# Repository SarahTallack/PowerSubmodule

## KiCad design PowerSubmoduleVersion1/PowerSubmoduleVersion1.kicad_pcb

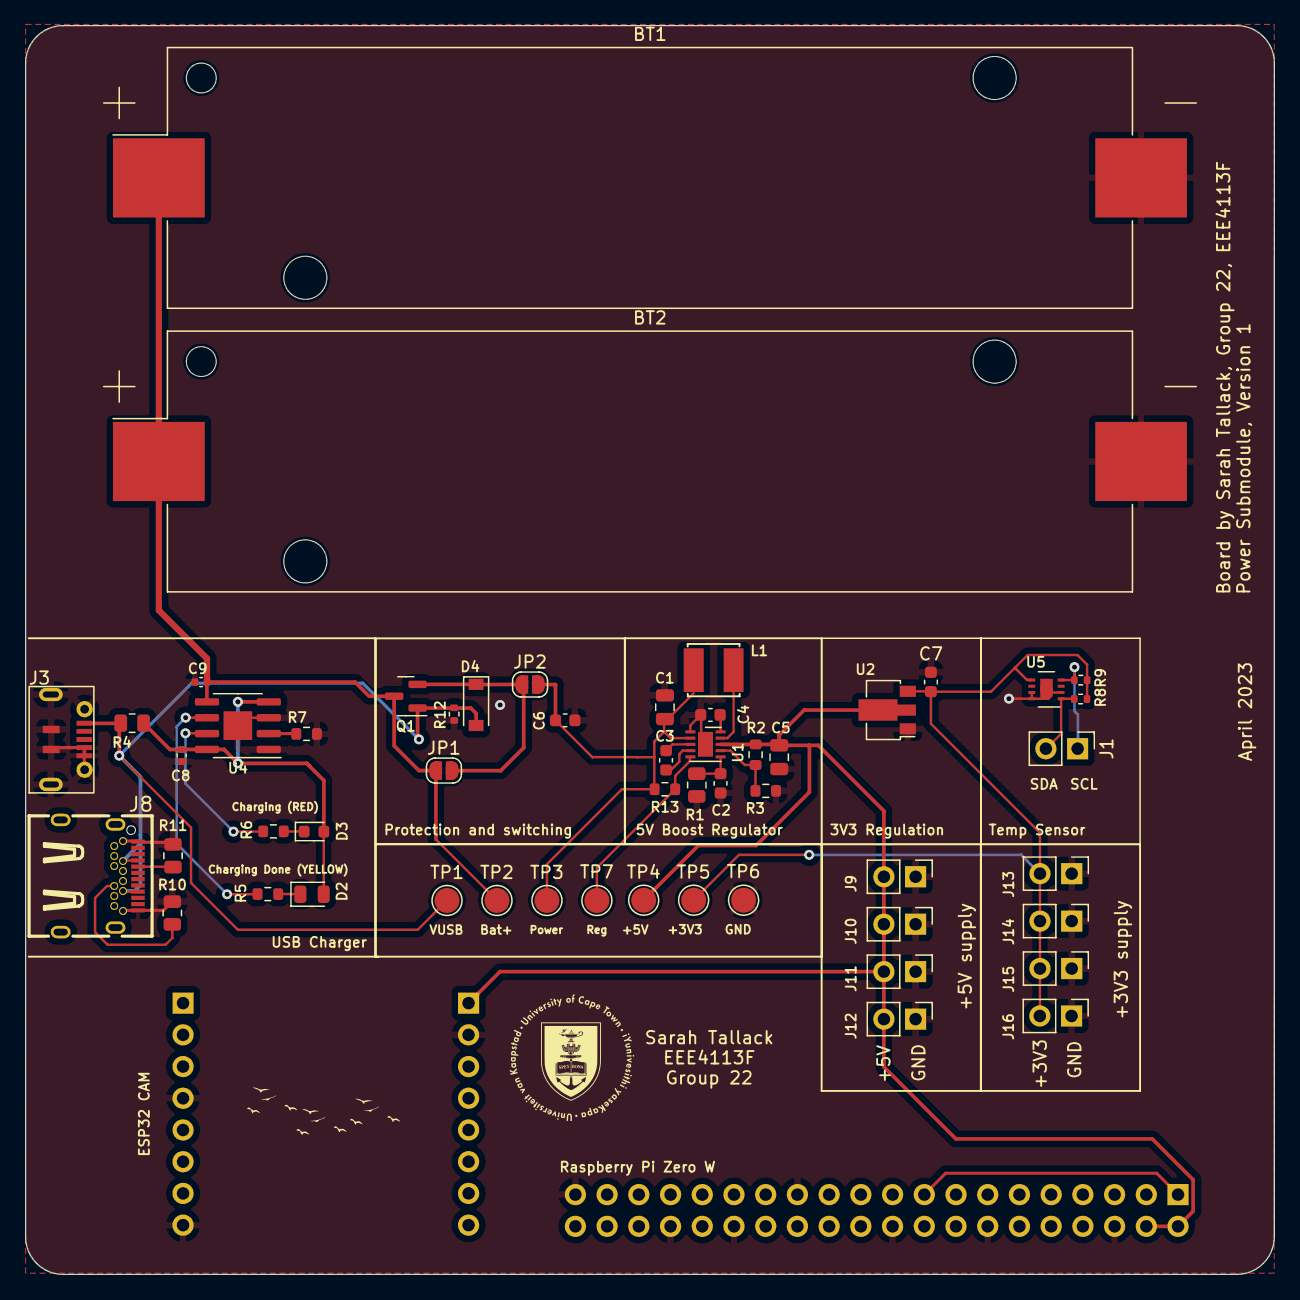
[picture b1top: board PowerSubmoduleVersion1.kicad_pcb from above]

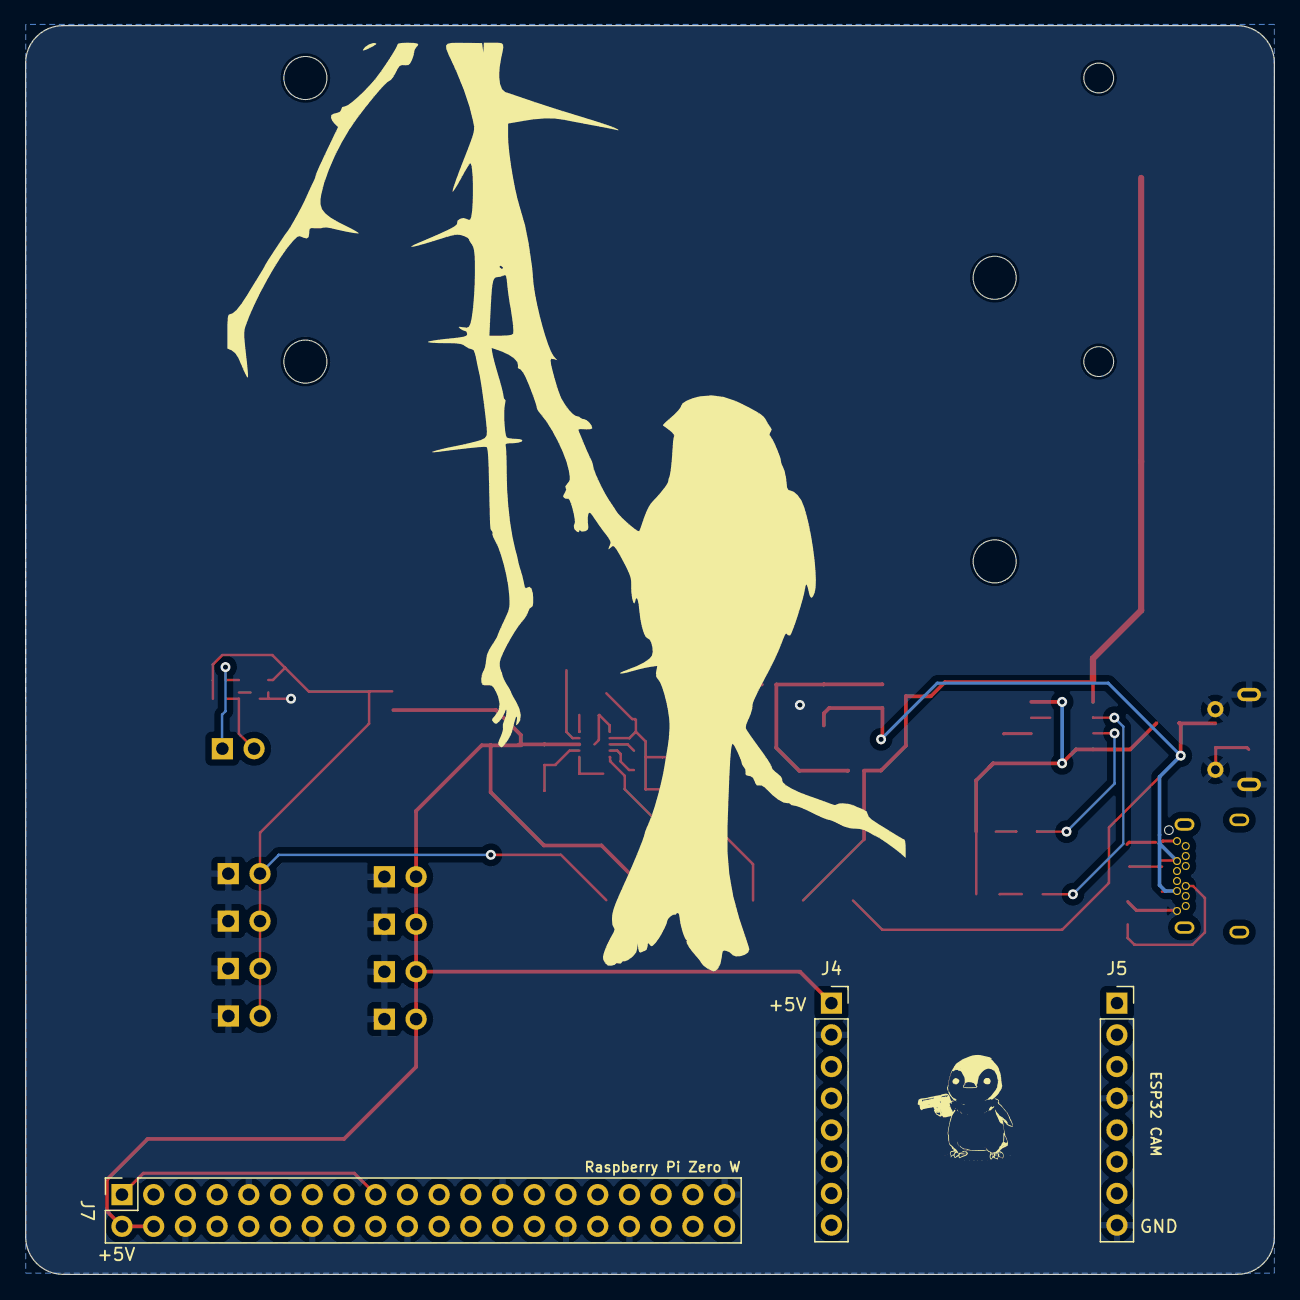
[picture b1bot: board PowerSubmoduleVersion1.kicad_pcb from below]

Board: 2 copper layers, 100.0 x 100.0 mm, 56 parts (3 on the bottom side), 25 nets.

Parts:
BT1, BT2: Li-Ion Battery; BatteryHolder_Keystone_1042_1x18650
C1: 4.7u; C_0805_2012Metric
C2, C3, C4, C6, C7: 100n; C_0603_1608Metric
C5: 1u; C_0805_2012Metric
C8, C9: 10uF; C_0402_1005Metric
D2: YLED; LED_0805_2012Metric
D3: RLED; LED_0603_1608Metric
D4: Diode; D_SOD-123
J1, J9, J10, J11, J12, J13, J14, J15, J16: Conn_01x02_Male; PinHeader_1x02_P2.54mm_Vertical
J3: USB_Micro_B_Female_Connector; C404969_Micro_USB
J4, J5: Conn_01x08_Male; PinSocket_1x08_P2.54mm_Vertical
J7: GPIO; PinSocket_2x20_P2.54mm_Vertical
J8: USB_C_Receptacle; USB-TYPE-C-TH_USB-306A-B-SU
JP1, JP2: Jumper_2_Open; SolderJumper-2_P1.3mm_Open_RoundedPad1.0x1.5mm
L1: 4.7u; IND-SMD_L4.0-W4.0
Q1: Si2301CDS; SOT-23
R1: 200k; R_0805_2012Metric
R2: 180k; R_0603_1608Metric
R3: 20k; R_0603_1608Metric
R4: 330m; R_0805_2012Metric
R5, R6, R13: 1k; R_0603_1608Metric
R7: 1.2k; R_0603_1608Metric
R8, R9: 10k; R_0402_1005Metric
R10, R11: 5.1k; R_0805_2012Metric
R12: 100k; R_0402_1005Metric
TP1, TP2, TP3, TP4, TP5, TP6, TP7: TestPoint; TestPoint_Pad_D2.0mm
U1: TPS63030DSKR; WSON-10-1EP_2.5x2.5mm_P0.5mm_EP1.2x2mm
U2: HT75xx-1-SOT89; SOT-89-3
U4: TP4056_1; HSOP-8-1EP_3.9x4.9mm_P1.27mm_EP2.3x2.3mm
U5: SHT30-DIS; Sensirion_DFN-8-1EP_2.5x2.5mm_P0.5mm_EP1.1x1.7mm

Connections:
/Microcontrollers/+3V3: J7.1, J7.17
/Microcontrollers/+5VReg: C5.2, J4.1, J7.2, J7.4, J9.2, J10.2, J11.2, J12.2, R2.1, TP4.1, U1.8 (OUT), U2.2 (VIN)
/Sensors/+3V3Reg: C7.1, J13.2, J14.2, J15.2, J16.2, R8.1, R9.1, TP5.1, U2.3 (VOUT), U5.5 (VDD)
/Sensors/SCL: J1.1, R9.2, U5.4 (SCL)
/Sensors/SDA: J1.2, R8.2, U5.1 (SDA)
/VoltageSupply/Bat+: BT1.1 (+), BT2.1 (+), C9.1, JP1.1 (A), Q1.3 (D), TP2.1, U4.5 (BAT)
/VoltageSupply/Power: C1.1, C6.1, JP2.2 (B), L1.1, R13.2, TP3.1, U1.2 (VIN)
/VoltageSupply/Reg: R13.1, TP7.1, U1.5 (EN)
/VoltageSupply/VUSB: D4.2 (A), J3.1 (VDD), J8.A4 (VBUS), J8.A9 (VBUS), J8.B4 (VBUS), J8.B9 (VBUS), Q1.1 (G), R4.1, R12.2, TP1.1
GND: BT1.2 (-), BT2.2 (-), C1.2, C2.1, C4.2, C5.1, C6.2, C7.2, C8.2, C9.2, J3.4 (ID), J3.5 (GND), J3.6, J4.2, J5.4, J5.8, J7.6, J7.9, J7.14, J7.20, J7.25, J7.30, J7.34, J7.39, J8.A1 (GND), J8.A12 (GND), J8.B1 (GND), J8.B12 (GND), J9.1, J10.1, J11.1, J12.1, J13.1, J14.1, J15.1, J16.1, R1.2, R3.2, R7.2, R10.1, R11.1, R12.1, TP6.1, U1.1 (GND), U1.11 (PGND), U2.1 (GND), U4.1 (TEMP), U4.3 (GND), U4.9 (EP), U5.2 (ADDR), U5.7 (R), U5.8 (VSS), U5.9 (PGND)
unnamed: C2.2, R1.1, U1.6 (SS)
unnamed: C3.1, U1.4 (CP1)
unnamed: C3.2, U1.3 (CP2)
unnamed: C4.1, U1.10 (VOUT)
unnamed: C8.1, D2.2 (A), D3.2 (A), R4.2, U4.4 (Vcc), U4.8 (CE)
unnamed: D2.1 (K), R5.1
unnamed: D3.1 (K), R6.1
unnamed: D4.1 (K), JP1.2 (B), JP2.1 (A), Q1.2 (S)
unnamed: J8.A5 (CC1), R11.2
unnamed: J8.B5 (CC2), R10.2
unnamed: L1.2, U1.9 (SW)
unnamed: R2.2, R3.1, U1.7 (FB)
unnamed: R5.2, U4.6 (STDBY)
unnamed: R6.2, U4.7 (CHRG)
unnamed: R7.1, U4.2 (PROG)

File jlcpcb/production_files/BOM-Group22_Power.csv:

Comment,Designator,Footprint,LCSC
Si2301CDS,Q1,SOT-23,C10487
HT75xx-1-SOT89,U2,SOT-89-3,C14289
10uF,"C8,C9",C_0402_1005Metric,C15525
TP4056_1,U4,HSOP-8-1EP_3.9x4.9mm_P1.27mm_EP2.3x2.3mm,C16581
200k,R1,R_0805_2012Metric,C17539
4.7u,C1,C_0805_2012Metric,C1779
4.7u,L1,IND-SMD_L4.0-W4.0,C206275
1k,"R13,R5,R6",R_0603_1608Metric,C21190
1.2k,R7,R_0603_1608Metric,C22765
180k,R2,R_0603_1608Metric,C22827
RLED,D3,LED_0603_1608Metric,C2286
YLED,D2,LED_0805_2012Metric,C2296
100k,R12,R_0402_1005Metric,C25741
10k,"R8,R9",R_0402_1005Metric,C25744
5.1k,"R10,R11",R_0805_2012Metric,C27834
1u,C5,C_0805_2012Metric,C28323
USB_C_Receptacle,J8,USB-TYPE-C-TH_USB-306A-B-SU,C309339
USB_Micro_B_Female_Connector,J3,C404969_Micro_USB,C404969
20k,R3,R_0603_1608Metric,C4184
100n,"C2,C3,C4,C6,C7",C_0603_1608Metric,C49678
330m,R4,R_0805_2012Metric,C52548
TPS63030DSKR,U1,WSON-10-1EP_2.5x2.5mm_P0.5mm_EP1.2x2mm,C60707
SHT30-DIS,U5,Sensirion_DFN-8-1EP_2.5x2.5mm_P0.5mm_EP1.1x1.7mm,C77361
Diode,D4,D_SOD-123,C8598
TestPoint,TP5,TestPoint_Pad_D2.0mm,
TestPoint,TP4,TestPoint_Pad_D2.0mm,
TestPoint,TP3,TestPoint_Pad_D2.0mm,
TestPoint,TP2,TestPoint_Pad_D2.0mm,
TestPoint,TP1,TestPoint_Pad_D2.0mm,
Li-Ion Battery,BT2,BatteryHolder_Keystone_1042_1x18650,
Li-Ion Battery,BT1,BatteryHolder_Keystone_1042_1x18650,
TestPoint,TP7,TestPoint_Pad_D2.0mm,
Conn_01x02_Male,J12,PinHeader_1x02_P2.54mm_Vertical,
TestPoint,TP6,TestPoint_Pad_D2.0mm,
Conn_01x02_Male,J15,PinHeader_1x02_P2.54mm_Vertical,
Conn_01x02_Male,J14,PinHeader_1x02_P2.54mm_Vertical,
Conn_01x02_Male,J16,PinHeader_1x02_P2.54mm_Vertical,
Conn_01x02_Male,J11,PinHeader_1x02_P2.54mm_Vertical,
Conn_01x02_Male,J13,PinHeader_1x02_P2.54mm_Vertical,
Conn_01x02_Male,J9,PinHeader_1x02_P2.54mm_Vertical,
Conn_01x02_Male,J10,PinHeader_1x02_P2.54mm_Vertical,
Conn_01x08_Male,J4,PinSocket_1x08_P2.54mm_Vertical,
GPIO,J7,PinSocket_2x20_P2.54mm_Vertical,
Conn_01x08_Male,J5,PinSocket_1x08_P2.54mm_Vertical,
Jumper_2_Open,JP2,SolderJumper-2_P1.3mm_Open_RoundedPad1.0x1.5mm,
Jumper_2_Open,JP1,SolderJumper-2_P1.3mm_Open_RoundedPad1.0x1.5mm,
Conn_01x02_Male,J1,PinHeader_1x02_P2.54mm_Vertical,

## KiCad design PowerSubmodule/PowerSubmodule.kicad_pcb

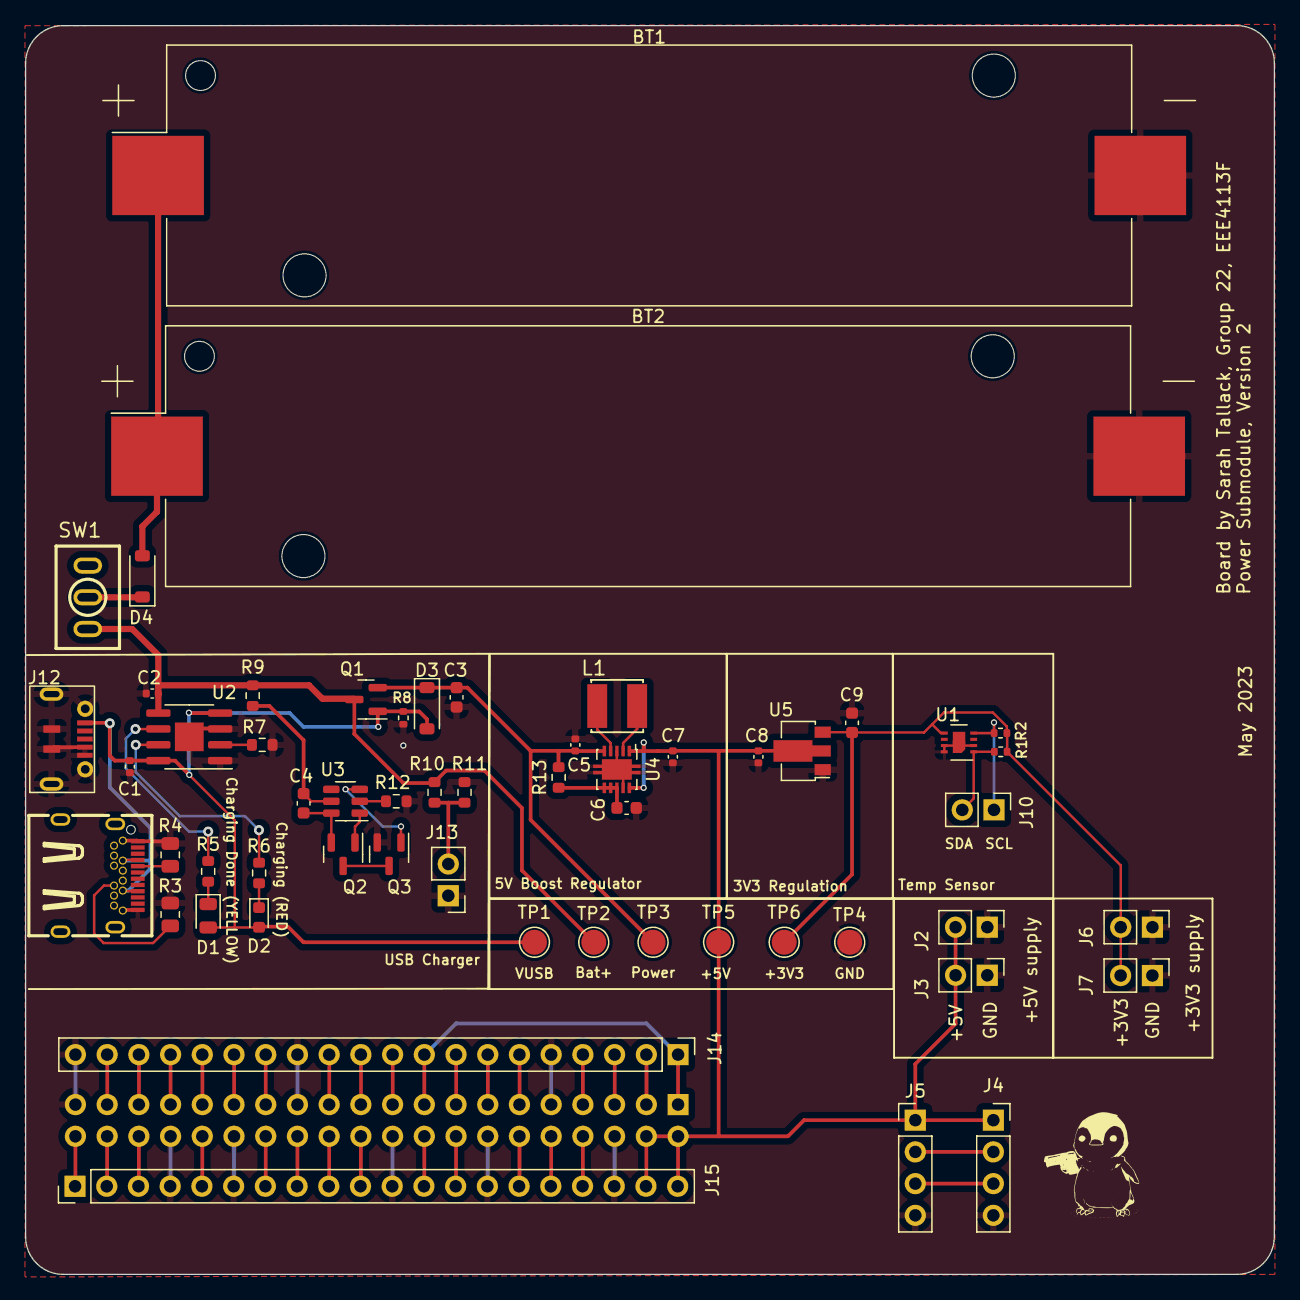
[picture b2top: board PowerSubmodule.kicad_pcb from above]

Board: 2 copper layers, 100.0 x 100.0 mm, 57 parts (1 on the bottom side), 58 nets.

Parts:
BT1, BT2: Li-Ion Battery; BatteryHolder_Keystone_1042_1x18650
C1, C2, C5, C7, C8: 10uF; C_0402_1005Metric
C3, C4, C6, C9: 100n; C_0603_1608Metric
D1: YLED; LED_0805_2012Metric
D2: RLED; LED_0603_1608Metric
D3, D4: Diode; D_SOD-123
J1: GPIO; PinSocket_2x20_P2.54mm_Vertical
J2, J3, J6, J7, J10, J13: Conn_01x02_Male; PinHeader_1x02_P2.54mm_Vertical
J4: Conn_01x04_Socket; PinSocket_1x04_P2.54mm_Vertical
J5: Conn_01x04_Pin; PinHeader_1x04_P2.54mm_Vertical
J11: USB_C_Receptacle; USB-TYPE-C-TH_USB-306A-B-SU
J12: USB_Micro_B_Female_Connector; C404969_Micro_USB
J14, J15: Conn_01x20_Pin; PinHeader_1x20_P2.54mm_Vertical
L1: 2.2u; IND-SMD_L4.0-W4.0
Q1: Si2301CDS; SOT-23
Q2, Q3: AO3400A; SOT-23
R1, R2: 10k; R_0402_1005Metric
R3, R4: 5.1k; R_0805_2012Metric
R5, R6, R12: 1k; R_0603_1608Metric
R7: 1.2k; R_0603_1608Metric
R8: 100k; R_0402_1005Metric
R9, R13: 100; R_0603_1608Metric
R10: 130k; R_0603_1608Metric
R11: 470k; R_0603_1608Metric
SW1: SW_SPDT_x2; SW-SPDT
TP1, TP2, TP3, TP4, TP5, TP6: TestPoint; TestPoint_Pad_D2.0mm
U1: SHT30-DIS; Sensirion_DFN-8-1EP_2.5x2.5mm_P0.5mm_EP1.1x1.7mm
U2: TP4056_1; HSOP-8-1EP_3.9x4.9mm_P1.27mm_EP2.3x2.3mm
U3: DW01A; SOT-23-6
U4: TPS63002; VSON-10-1EP_3x3mm_P0.5mm_EP1.65x2.4mm
U5: HT75xx-1-SOT89; SOT-89-3

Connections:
/+3V3: J1.1, J1.17, J14.1, J14.9
/+5VReg: C7.1, C8.1, J1.2, J1.4, J2.2, J3.2, J4.1, J5.1, J15.19, J15.20, TP5.1, U4.1 (VOUT), U4.10 (FB), U5.2 (VIN)
/BatteryCharging/Bat+: C2.1, Q1.3 (D), R9.1, R10.1, SW1.1 (A), TP2.1, U2.5 (BAT)
/BatteryCharging/BatIn: BT1.1 (+), BT2.1 (+), D4.2 (A)
/BatteryCharging/BatLevel: J13.2, R10.2, R11.1
/BatteryCharging/Power: C3.1, C5.1, D3.1 (K), Q1.2 (S), R13.1, TP3.1, U4.5 (VIN)
/BatteryCharging/VUSB: C1.1, D1.2 (A), D2.2 (A), D3.2 (A), J11.A4 (VBUS), J11.A9 (VBUS), J11.B4 (VBUS), J11.B9 (VBUS), J12.1 (VDD), Q1.1 (G), R8.2, TP1.1, U2.4 (Vcc), U2.8 (CE)
/DT: J4.3, J5.3
/GPIO26: J1.37, J14.19
/GPIO[2]/SDA1: J1.3, J14.2
/GPIO[3]/SCL1: J1.5, J14.3
/GPIO[4]/GPCLK0: J1.7, J14.4
/GPIO[5]: J1.29, J14.15
/GPIO[6]: J1.31, J14.16
/GPIO[7]/SPI0.CE1: J1.26, J15.8
/GPIO[8]/SPI0.CE0: J1.24, J15.9
/GPIO[9]/SPI0.MISO: J1.21, J14.11
/GPIO[10]/SPI0.MOSI: J1.19, J14.10
/GPIO[11]/SPI0.SCLK: J1.23, J14.12
/GPIO[12]/PWM0: J1.32, J15.5
/GPIO[13]/PWM1: J1.33, J14.17
/GPIO[14]/TXD0: J1.8, J15.17
/GPIO[15]/RXD0: J1.10, J15.16
/GPIO[16]: J1.36, J15.3
/GPIO[17]: J1.11, J14.6
/GPIO[18]/PCM.CLK: J1.12, J15.15
/GPIO[19]/PCM.FS: J1.35, J14.18
/GPIO[20]/PCM.DIN: J1.38, J15.2
/GPIO[21]/PCM.DOUT: J1.40, J15.1
/GPIO[22]: J1.15, J14.8
/GPIO[23]: J1.16, J15.13
/GPIO[24]: J1.18, J15.12
/GPIO[25]: J1.22, J15.10
/GPIO[27]: J1.13, J14.7
/ID_SCL: J1.28, J15.7
/ID_SDA: J1.27, J14.14
/SCK: J4.2, J5.2
/Sensors/+3V3Reg: C9.1, J6.2, J7.2, R1.1, R2.1, TP6.1, U1.5 (VDD), U5.3 (VOUT)
/Sensors/SCL: J10.1, R2.2, U1.4 (SCL)
/Sensors/SDA: J10.2, R1.2, U1.1 (SDA)
GND: BT1.2 (-), BT2.2 (-), C1.2, C2.2, C3.2, C5.2, C6.1, C7.2, C8.2, C9.2, J1.6, J1.9, J1.14, J1.20, J1.25, J1.30, J1.34, J1.39, J2.1, J3.1, J4.4, J5.4, J6.1, J7.1, J11.A1 (GND), J11.A12 (GND), J11.B1 (GND), J11.B12 (GND), J12.4 (ID), J12.5 (GND), J12.6, J13.1, J14.5, J14.13, J14.20, J15.4, J15.6, J15.11, J15.14, J15.18, Q3.2 (S), R3.1, R4.1, R7.2, R8.1, R11.2, R12.2, TP4.1, U1.2 (ADDR), U1.7 (R), U1.8 (VSS), U1.9 (PGND), U2.1 (TEMP), U2.3 (GND), U2.9 (EP), U4.3 (PGND), U4.9 (GND), U4.11 (PGND), U5.1 (GND)
unnamed: D1.1 (K), R5.1
unnamed: D2.1 (K), R6.1
unnamed: D4.1 (K), SW1.2 (B)
unnamed: J11.A5 (CC1), R4.2
unnamed: J11.B5 (CC2), R3.2
unnamed: Q2.3 (D), Q3.3 (D)
unnamed: Q2.1 (G), U3.1 (OD)
unnamed: C4.1, Q2.2 (S), U3.6 (GND)
unnamed: Q3.1 (G), U3.3 (OC)
unnamed: R6.2, U2.7 (CHRG)
unnamed: R7.1, U2.2 (PROG)
unnamed: R5.2, U2.6 (STDBY)
unnamed: C4.2, R9.2, U3.5 (VCC)
unnamed: R12.1, U3.2 (VM)
unnamed: C6.2, R13.2, U4.6 (EN), U4.7 (PS/SYNC), U4.8 (VINA)
unnamed: L1.2, U4.4 (L1)
unnamed: L1.1, U4.2 (L2)

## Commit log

2023-05-20 Version 1
2023-05-21 Version 2 complete
